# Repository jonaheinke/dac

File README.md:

# DAC with Headphone Amplifier

## Introduction

## Schematic preview

### Main schematic

### Left amplifier (right channel is identical)

### Power supply

### Front plate

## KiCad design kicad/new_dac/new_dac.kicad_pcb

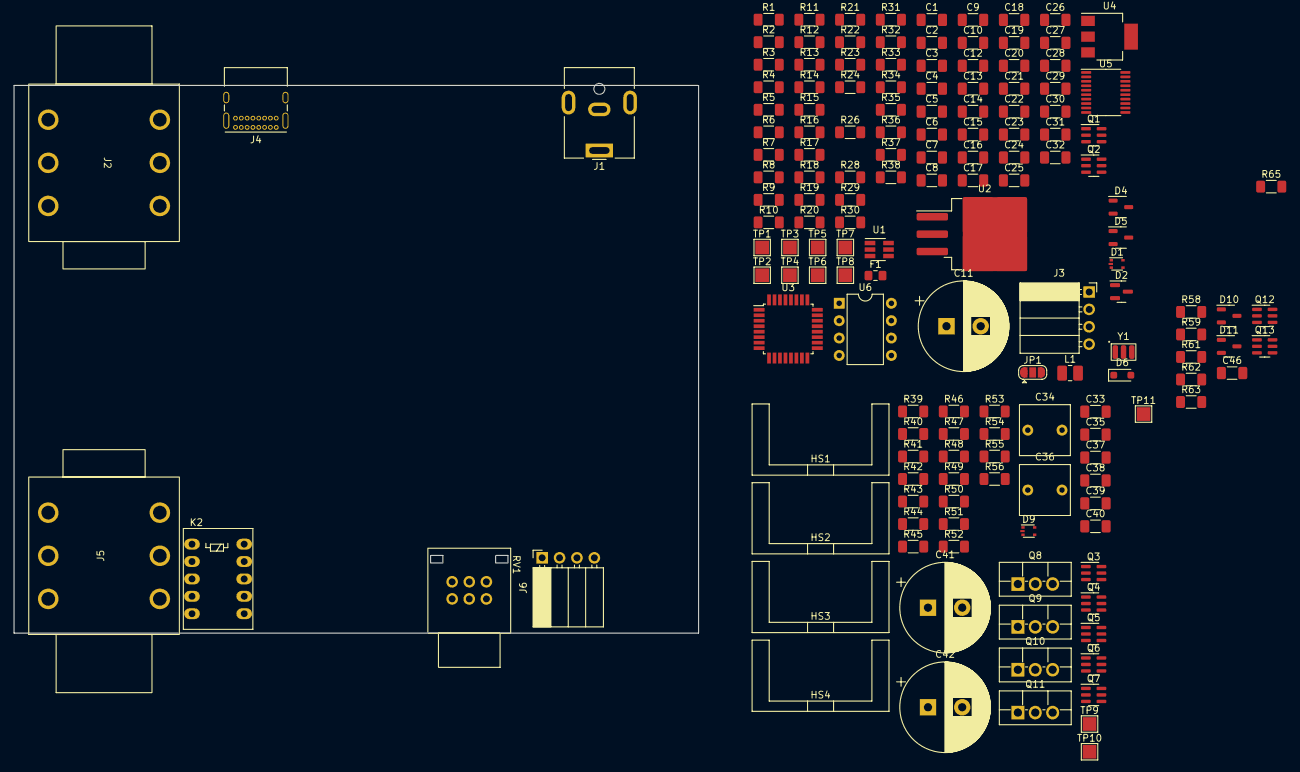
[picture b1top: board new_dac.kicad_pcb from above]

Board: 4 copper layers, 100.0 x 80.0 mm, 158 parts (1 on the bottom side), 92 nets, no tracks yet.

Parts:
C1, C7, C9, C10, C14, C15, C18, C21, C32, C37, C38: 100n; C_1206_3216Metric_Pad1.33x1.80mm_HandSolder
C2, C5, C6, C8, C12, C13, C16, C19, C22, C23, C24, C28, C29, C35: 10u; C_1206_3216Metric_Pad1.33x1.80mm_HandSolder
C3, C4, C25, C30, C31: 15n; C_1206_3216Metric_Pad1.33x1.80mm_HandSolder
C11: 470u; CP_Radial_D13.0mm_P5.00mm
C17, C20, C26, C46: 2u2; C_1206_3216Metric_Pad1.33x1.80mm_HandSolder
C27: 1n; C_1206_3216Metric_Pad1.33x1.80mm_HandSolder
C33: 4u7; C_1206_3216Metric_Pad1.33x1.80mm_HandSolder
C34: 4u7; C_Rect_L7.2mm_W7.2mm_P5.00mm_FKS2_FKP2_MKS2_MKP2
C36: 10u; C_Rect_L7.2mm_W7.2mm_P5.00mm_FKS2_FKP2_MKS2_MKP2
C39, C40: 470u; C_1206_3216Metric_Pad1.33x1.80mm_HandSolder
C41, C42: 10u; CP_Radial_D13.0mm_P5.00mm
D1, D9: QUAD_TVS_5V; SOT-665
D2, D7: DUAL_TVS_15V; SOT-23
D4, D5: D; SOT-23-3
D6: D; D_SOD-323_HandSoldering
D10, D11: SOT-23-3
F1: 500mA; Fuse_0805_2012Metric_Pad1.15x1.40mm_HandSolder
HS1, HS2, HS3, HS4: Heatsink; Heatsink_Boyd_507302B00000G
J1: USB_C_Receptacle_USB2.0; BarrelJack_CUI_PJ-063AH_Horizontal
J2: Barrel_Jack_Switch; Audio_Jack_SJ-6307
J3: Conn_01x04; PinSocket_1x04_P2.54mm_Horizontal
J4: USB_C_Receptacle_USB2.0; USB_C_Receptacle_GCT_USB4085
J5: AudioJack3_Switch; Audio_Jack_SJ-6307
J6: AudioJack3_Switch; PinSocket_1x04_P2.54mm_Horizontal
JP1: Ground_Jumper; SolderJumper-3_P1.3mm_Open_RoundedPad1.0x1.5mm
K2: DPDT_Relay; Relay_DPDT_FRT5
L1: 6u8; L_1008_2520Metric_Pad1.43x2.20mm_HandSolder
Q1, Q5, Q6, Q7, Q12: BCM56DS; SC-74-6_1.5x2.9mm_P0.95mm
Q2, Q3, Q4, Q13: BCM53DS; SC-74-6_1.5x2.9mm_P0.95mm
Q8, Q9, Q10, Q11: 2SC4511; TO-220F-3_Vertical
R1, R2: 5k1; R_1206_3216Metric_Pad1.30x1.75mm_HandSolder
R3, R7, R30, R39, R41: 1k5; R_1206_3216Metric_Pad1.30x1.75mm_HandSolder
R4, R5: 22; R_1206_3216Metric_Pad1.30x1.75mm_HandSolder
R6, R10: 430k; R_1206_3216Metric_Pad1.30x1.75mm_HandSolder
R8, R9, R32: 1M; R_1206_3216Metric_Pad1.30x1.75mm_HandSolder
R11: 3k9; R_1206_3216Metric_Pad1.30x1.75mm_HandSolder
R12, R24, R31: 680; R_1206_3216Metric_Pad1.30x1.75mm_HandSolder
R13, R16, R19, R22, R33, R34, R37, R38, R43, R45, R55, R56, R61: 22k; R_1206_3216Metric_Pad1.30x1.75mm_HandSolder
R14, R15, R20, R53, R54, R62: 100k; R_1206_3216Metric_Pad1.30x1.75mm_HandSolder
R17, R18, R26, R51, R52: 15; R_1206_3216Metric_Pad1.30x1.75mm_HandSolder
R21, R44, R46, R63: 10k; R_1206_3216Metric_Pad1.30x1.75mm_HandSolder
R23, R47, R48, R65: 2k2; R_1206_3216Metric_Pad1.30x1.75mm_HandSolder
R28, R29, R49, R50: 8R2; R_1206_3216Metric_Pad1.30x1.75mm_HandSolder
R35, R36, R40, R42: 4k3; R_1206_3216Metric_Pad1.30x1.75mm_HandSolder
R58, R59: 47k; R_1206_3216Metric_Pad1.30x1.75mm_HandSolder
RV1: 10k; RK09L12B
TP1: VBUS; TestPoint_Pad_2.0x2.0mm
TP2: +24; TestPoint_Pad_2.0x2.0mm
TP3: +5V; TestPoint_Pad_2.0x2.0mm
TP4: +22; TestPoint_Pad_2.0x2.0mm
TP5: GND; TestPoint_Pad_2.0x2.0mm
TP6, TP11: +3V3; TestPoint_Pad_2.0x2.0mm
TP7: -3V3; TestPoint_Pad_2.0x2.0mm
TP8: 1V8; TestPoint_Pad_2.0x2.0mm
TP9: VAS_L; TestPoint_Pad_2.0x2.0mm
TP10: VAS_R; TestPoint_Pad_2.0x2.0mm
U1: BD9G101G; SOT-23-6_Handsoldering
U2: LT3088; TO-263-3_TabPin2
U3: PCM2706CPJTR; TQFP-32_7x7mm_P0.8mm
U4: TLV1117LV-33; SOT-223-3_TabPin2
U5: PCM5102A; TSSOP-20_4.4x6.5mm_P0.65mm
U6: LM555xN; DIP-8_W7.62mm
Y1: 12MHz±0.05%; Resonator_Murata

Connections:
+3V3: C7.2, C12.1, C13.1, C14.1, C15.1, C16.1, C21.1, C22.1, R3.2, R7.2, TP6.1, TP11.1, U3.10 (TEST), U3.16 (PSEL), U3.21 (VDD), U3.24 (VBUS), U4.2 (VO), U5.1 (CPVDD), U5.8 (AVDD), U5.20 (DVDD)
+5V: C6.1, C10.1, L1.2, R11.1, R23.1, R33.1, TP3.1, U4.3 (VI), U6.4 (R), U6.8 (VCC)
+20Vreg: C5.1, C11.1, Q3.5 (E1), Q4.5 (E1), Q5.3 (C2), Q6.3 (C2), Q8.2 (C), Q10.2 (C), R13.1, R39.1, R41.1, R47.1, R48.1, TP4.1, U2.2 (OUT)
+24V: C2.1, C26.1, C46.1, J3.1, Q2.5 (E1), Q13.4 (E2), R6.1, R16.1, R20.1, R61.1, R62.1, TP2.1, U1.4 (EN), U1.5 (VCC), U2.3 (IN)
/AMP_L: C39.2, R14.1, R17.1
/AMP_R: C40.2, R15.1, R18.1
/AUDIO_OUT_L: D7.2 (A2), J5.T, K2.8, R28.2
/AUDIO_OUT_R: D7.1 (A1), J5.R, K2.3, R29.2
/BCK: U3.19 (FUNC1), U5.13 (BCK)
/BST: C4.1, U1.1 (BST)
/CAPM: C17.2, U5.4 (CAPM)
/CAPP: C17.1, U5.2 (CAPP)
/CONN_D+: D1.4 (A3), J4.A6 (D+), J4.B6 (D+), R3.1, R5.1
/CONN_D-: D1.3 (A2), J4.A7 (D-), J4.B7 (D-), R4.1
/D+: R5.2, U3.23 (D+)
/D-: R4.2, U3.22 (D-)
/DAC_OUT_L: D9.1 (A1), U5.6 (OUTL)
/DAC_OUT_R: D9.4 (A3), U5.7 (OUTR)
/DATA: U3.17 (DOUT), U5.14 (DIN)
/DC_FUSED: D2.2 (A2), F1.2
/DC_LP_L: C23.1, D4.2 (A), R14.2
/DC_LP_R: C24.1, D5.2 (A), R15.2
/DT: R7.1, U3.15 (DT)
/FEEDBACK: C10.2, R11.2, R12.1, U1.3 (FB)
/LDOO: C18.1, C19.1, TP8.1, U5.18 (LDOO)
/LRCK: U3.5 (FUNC0), U5.15 (LRCK)
/PROT_ARC_L: C28.2, R28.1
/PROT_ARC_R: C29.2, R29.1
/RELAY: K2.1, Q2.6 (C1), R65.1
/RLY_IN_L: C28.1, K2.7, R17.2, R19.2
/RLY_IN_R: C29.1, K2.4, R18.2, R22.2
/Reg_Set: C3.1, R10.1, U2.1 (SET)
/SCK: U3.18 (FUNC2), U5.12 (SCK)
/SSPND: J3.2, U3.11 (~SSPND), U5.17 (XSMT)
/SWITCHING: C4.2, L1.1, U1.6 (LX)
/USB_SHIELD: D1.2 (C), J4.S1 (SHIELD), JP1.3 (B)
/VCCP: C9.2, U3.2 (VCCP)
/VCOM: C8.2, U3.32 (VCOM)
/VNEG: C20.1, TP7.1, U5.5 (VNEG)
/XTI: R8.1, U3.12 (XTI), Y1.1
/XTO: R8.2, U3.13 (XTO), Y1.3
/amplifier/AUDIO_IN_L: D9.3 (A2), RV1.1
/amplifier/AUDIO_IN_R: D9.5 (A4), RV1.4
/amplifier/FB_L: Q5.1 (B1), R35.2, R43.2, R44.1
/amplifier/FB_R: Q6.1 (B1), R36.2, R45.2, R46.1
/amplifier/OPS_L: C39.1, Q8.3 (E), Q9.2 (C), R43.1, R51.1
/amplifier/OPS_R: C40.1, Q10.3 (E), Q11.2 (C), R45.1, R52.1
/amplifier/VAS_L: Q3.3 (C2), Q5.2 (B2), Q5.6 (C1), TP9.1
/amplifier/VAS_R: Q4.3 (C2), Q6.2 (B2), Q6.6 (C1), TP10.1
/old_design/DC_LP_L: C41.1, R53.2, R55.1
/old_design/DC_LP_R: C42.1, R54.2, R56.1
/old_design/DC_NEG: D10.1 (A), D11.1 (A), Q13.1 (B1)
/old_design/DC_POS: D10.3 (K), D11.3 (K), Q12.1 (B1)
/old_design/DC_VD_L: D10.2 (common), R55.2, R58.1
/old_design/DC_VD_R: D11.2 (common), R56.2, R59.1
GND: C2.2, C3.2, C5.2, C6.2, C11.2, C12.2, C35.2, C36.2, C37.2, C38.2, D2.1 (A1), D7.3 (common), D9.2 (C), J3.4, J5.S, J5.SN, JP1.1 (A), Q7.4 (E2), Q7.5 (E1), R6.2, R10.2, R12.2, R13.2, R19.1, R22.1, R37.2, R38.2, R40.2, R42.2, R44.2, R46.2, R49.2, R50.2, RV1.3, RV1.6, TP5.1, U1.2 (GND), U4.1 (GND)
GNDD: C1.2, C7.1, C8.1, C9.1, C13.2, C14.2, C15.2, C16.2, C18.2, C19.2, C20.2, C21.2, C22.2, C23.2, C24.2, C25.2, C27.2, C30.2, C32.2, C41.2, C42.2, D1.5 (A4), D6.2 (A), J4.A1 (GND), J4.A12 (GND), J4.B1 (GND), J4.B12 (GND), JP1.2 (C), K2.2, K2.9, K2.10, Q1.4 (E2), Q1.5 (E1), Q12.4 (E2), Q12.5 (E1), Q13.6 (C1), R1.2, R2.2, R9.1, R31.2, R32.2, R34.2, R58.2, R59.2, U3.1 (PGND), U3.9 (FSEL), U3.20 (DGND), U3.25 (ZGND), U3.26 (AGNDL), U3.31 (AGNDR), U5.3 (CPGND), U5.9 (AGND), U5.10 (DEMP), U5.11 (FLT), U5.16 (FMT), U5.19 (DGND), U6.1 (GND), Y1.2
unnamed: C33.1, RV1.2
unnamed: C33.2, R35.1
unnamed: C34.1, RV1.5
unnamed: C34.2, R36.1
unnamed: C37.1, R51.2
unnamed: C38.1, R52.2
unnamed: D4.1 (K), D5.1 (K), Q1.1 (B1)
unnamed: D6.1 (K), R65.2
unnamed: C32.1, R32.1
unnamed: Q1.2 (B2), Q1.6 (C1), R16.2
unnamed: C26.2, Q1.3 (C2), R21.2
unnamed: Q2.1 (B1), R20.2, R21.1
unnamed: Q3.1 (B1), Q3.4 (E2), R39.2
unnamed: Q3.2 (B2), Q3.6 (C1), R37.1
unnamed: Q4.1 (B1), Q4.4 (E2), R41.2
unnamed: Q4.2 (B2), Q4.6 (C1), R38.1
unnamed: C35.1, Q5.5 (E1), R40.1
unnamed: Q5.4 (E2), Q8.1 (B)
unnamed: C36.1, Q6.5 (E1), R42.1
unnamed: Q7.1 (B1), Q9.3 (E), R49.1
unnamed: Q7.6 (C1), Q9.1 (B), R47.2
unnamed: Q6.4 (E2), Q10.1 (B)
unnamed: Q7.3 (C2), Q11.1 (B), R48.2
unnamed: Q7.2 (B2), Q11.3 (E), R50.1
unnamed: Q12.2 (B2), Q12.6 (C1), Q13.5 (E1), R61.2
unnamed: C46.2, Q12.3 (C2), R63.2
unnamed: Q13.2 (B2), R62.2, R63.1
unnamed: C25.1, U6.5 (CV)
unnamed: R23.2, R24.1, U6.7 (DIS)
unnamed: R26.1, U6.3 (Q)
unnamed: C27.1, R24.2, U6.2 (TR), U6.6 (THR)
unnamed: C30.1, R26.2
unnamed: C31.2, R31.1
unnamed: R33.2, R34.1
VBUS: C1.1, D1.1 (A1), J4.A4 (VBUS), J4.A9 (VBUS), J4.B4 (VBUS), J4.B9 (VBUS), R9.2, TP1.1, U3.3 (HOST)

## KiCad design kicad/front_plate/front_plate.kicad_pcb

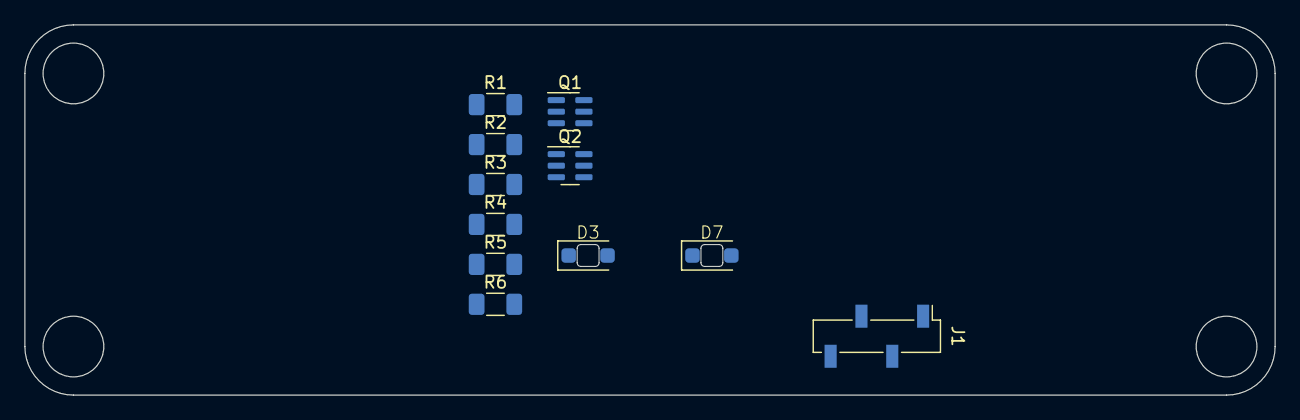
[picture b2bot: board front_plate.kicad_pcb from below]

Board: 2 copper layers, 103.0 x 30.5 mm, 11 parts (11 on the bottom side), 11 nets, no tracks yet.

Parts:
D3, D7: AMBER; LED_Harvatek_B2601
J1: Conn_01x04; PinSocket_1x04_P2.54mm_Vertical_SMD_Pin1Left
Q1, Q2: BCM56DS; SC-74-6_1.5x2.9mm_P0.95mm
R1: 47k; R_1206_3216Metric_Pad1.30x1.75mm_HandSolder
R2, R4, R5: 2k2; R_1206_3216Metric_Pad1.30x1.75mm_HandSolder
R3: 10k; R_1206_3216Metric_Pad1.30x1.75mm_HandSolder
R6: 4k3; R_1206_3216Metric_Pad1.30x1.75mm_HandSolder

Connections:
+24V: J1.1, R1.2, R3.2, R4.2, R5.2
/ANALOG: J1.3, Q1.1 (B1), R1.1, R2.2
/USB: J1.2, R6.1
GND: J1.4, Q1.4 (E2), Q1.5 (E1), Q2.4 (E2), R2.1
unnamed: D3.2 (A), R4.1
unnamed: D3.1 (K), Q1.3 (C2)
unnamed: D7.2 (A), R5.1
unnamed: D7.1 (K), Q2.6 (C1)
unnamed: Q1.2 (B2), Q1.6 (C1), Q2.2 (B2), R3.1
unnamed: Q2.1 (B1), R6.2
unnamed: Q2.3 (C2), Q2.5 (E1)

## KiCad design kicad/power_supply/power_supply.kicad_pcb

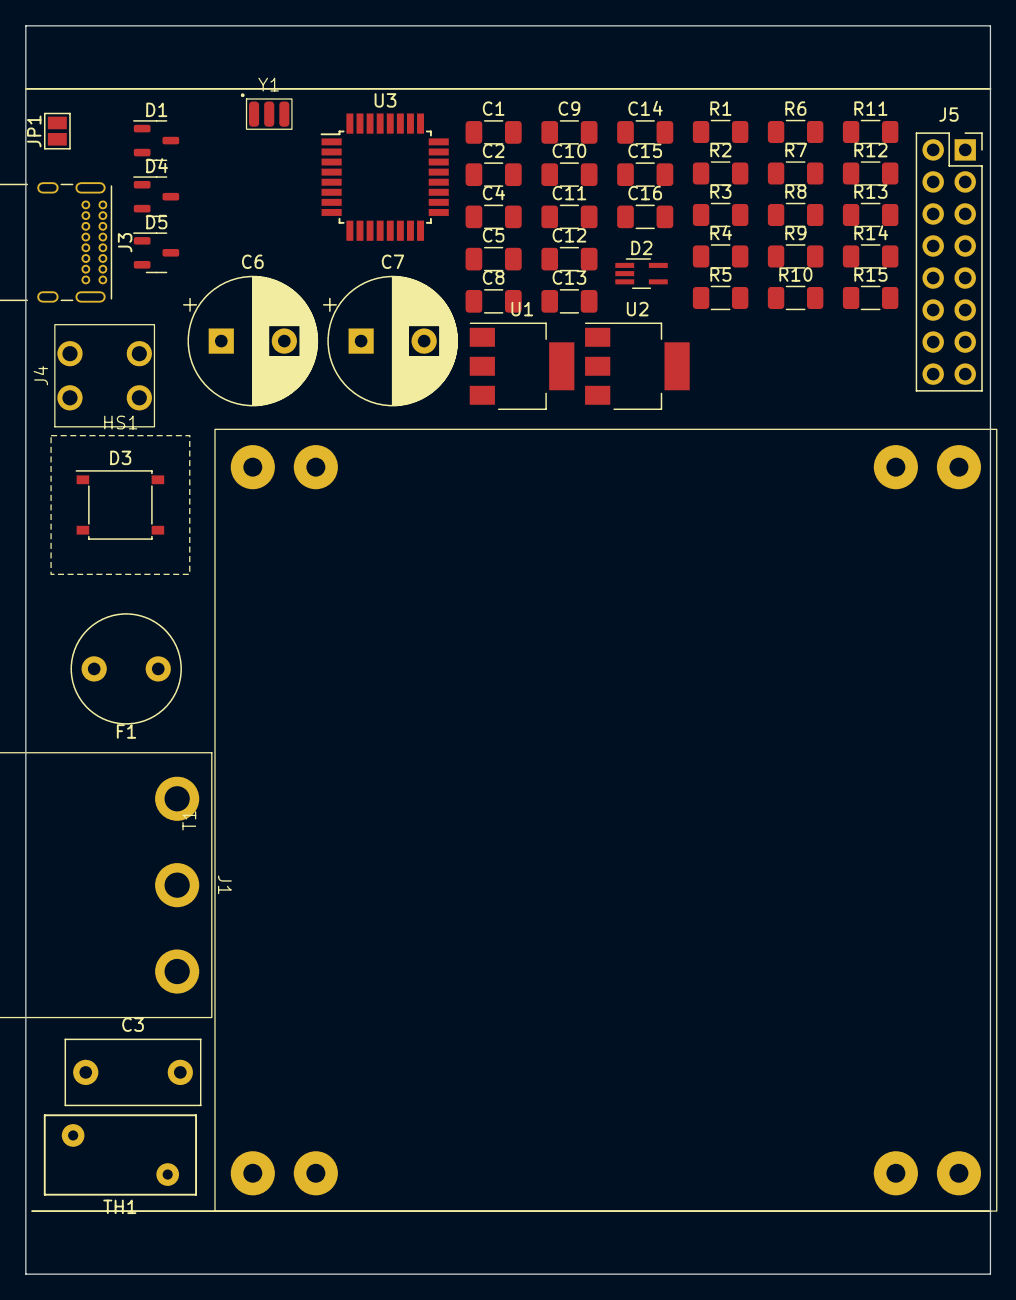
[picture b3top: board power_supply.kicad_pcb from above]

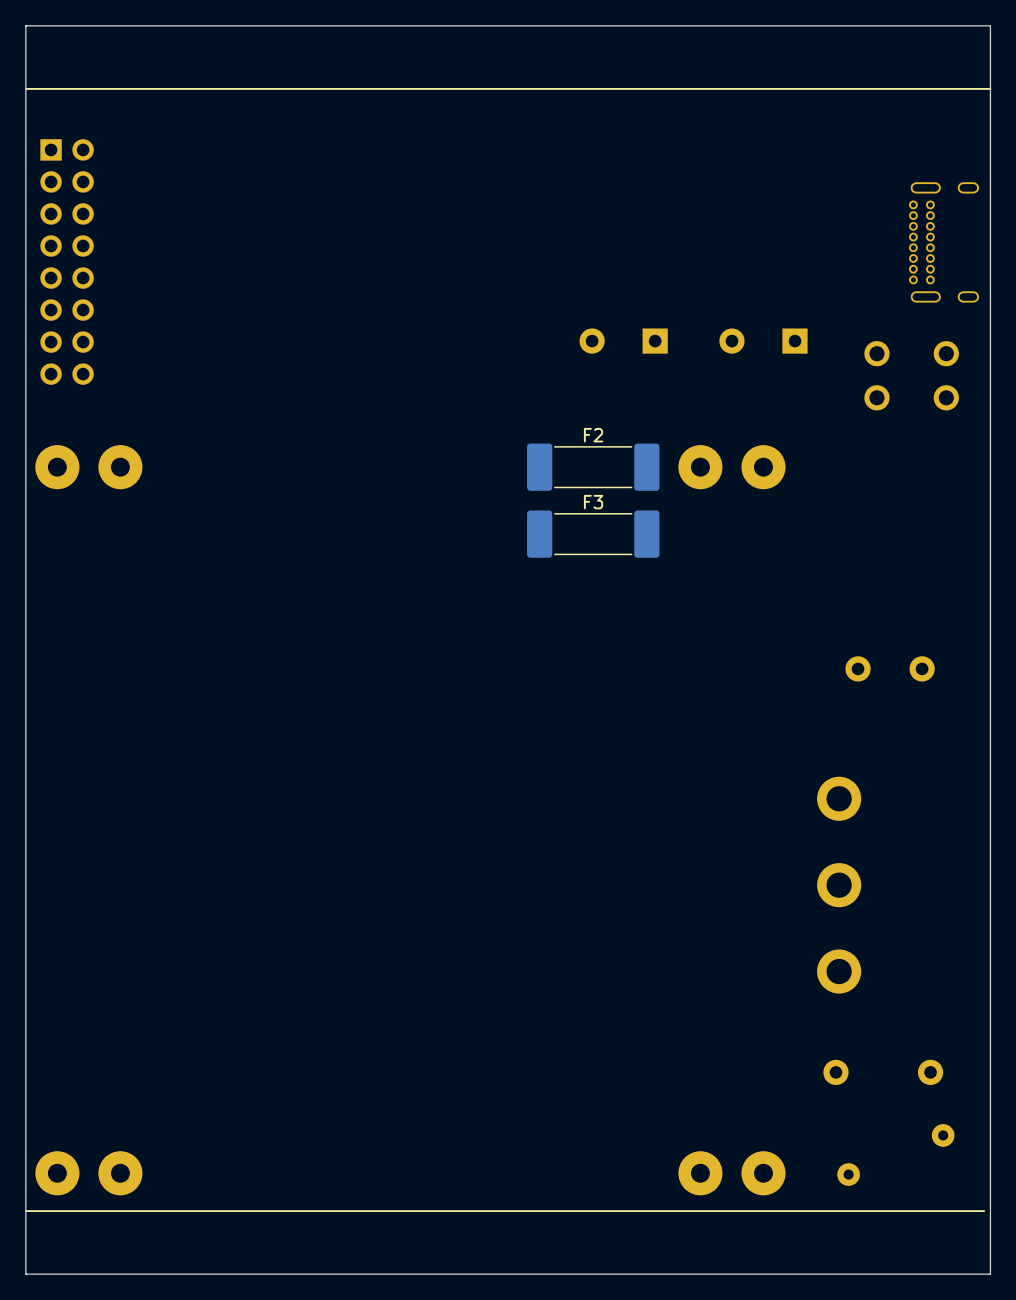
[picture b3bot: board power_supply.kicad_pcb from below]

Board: 2 copper layers, 76.5 x 99.0 mm, 51 parts (2 on the bottom side), 34 nets, no tracks yet.

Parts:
C1, C4, C8, C10, C13, C14: 100n; C_1206_3216Metric_Pad1.33x1.80mm_HandSolder
C2: 4n7; C_1206_3216Metric_Pad1.33x1.80mm_HandSolder
C3: 3n9; C_Disc_D10.5mm_W5.0mm_P7.50mm
C5: 3u3; C_1206_3216Metric_Pad1.33x1.80mm_HandSolder
C6, C7: 470u; CP_Radial_D10.0mm_P5.00mm
C9, C11, C12, C15, C16: 10u; C_1206_3216Metric_Pad1.33x1.80mm_HandSolder
D1, D4, D5: SOT-23-3
D2: D_TVS_Quadruple; SOT-353_SC-70-5_Handsoldering
D3: Diode_Bridge_Vishay_MBLS
F1: 80mA; Fuse_Littelfuse_372_D8.50mm
F2, F3: 500mA; Fuse_Schurter_UMT250
HS1: Heatsink; Heatsink_10x10
J1: Conn_WallSocket_Earth; WallSocket_Schurter_6160.0003
J3: USB_C_Receptacle_USB2.0; USB_C_Receptacle_GCT_USB4085
J4: Conn_01x02; WAGO_2086-11X2
J5: Conn_02x08_Odd_Even; PinSocket_2x08_P2.54mm_Vertical
JP1: Jumper_2_Open; SolderJumper-2_P1.3mm_Open_Pad1.0x1.5mm
R1, R6, R7: 22; R_1206_3216Metric_Pad1.30x1.75mm_HandSolder
R2: 33k; R_1206_3216Metric_Pad1.30x1.75mm_HandSolder
R3, R4: 5k1; R_1206_3216Metric_Pad1.30x1.75mm_HandSolder
R5, R8: 1k5; R_1206_3216Metric_Pad1.30x1.75mm_HandSolder
R9, R10: 10k; R_1206_3216Metric_Pad1.30x1.75mm_HandSolder
R11: 1M; R_1206_3216Metric_Pad1.30x1.75mm_HandSolder
R12, R15: 100; R_1206_3216Metric_Pad1.30x1.75mm_HandSolder
R13, R14: 1k1; R_1206_3216Metric_Pad1.30x1.75mm_HandSolder
T1: 70063K; Talema_Transformer_2P2S_25VA
TH1: MOV; RV_Disc_D12mm_W6.3mm_P7.5mm
U1: LM317_SOT-223; SOT-223-3_TabPin2
U2: LM337_SOT223; SOT-223-3_TabPin2
U3: PCM2706CPJTR; TQFP-32_7x7mm_P0.8mm
Y1: 12MHz±0.05%; Resonator_Murata

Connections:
+3V3: C8.2, R5.2, R8.2, U3.10 (TEST), U3.16 (PSEL), U3.21 (VDD)
+20Vreg: C13.1, C15.1, D4.2 (common), J5.1, R12.1, U1.2 (VO)
+25V: C6.1, D4.3 (K), F2.2, J5.2, R9.1, U1.3 (VI)
-20Vreg: C14.2, C16.2, D5.2 (common), J5.5, R15.2, U2.3 (VO)
-25V: C7.2, D5.1 (A), F3.2, J5.6, R10.2, U2.2 (VI)
/BCK: J5.15, U3.19 (FUNC1)
/CONN_D+: D2.4 (A3), J3.A6 (D+), J3.B6 (D+), R5.1, R7.1
/CONN_D-: D2.3 (A2), J3.A7 (D-), J3.B7 (D-), R6.1
/D+: R7.2, U3.23 (D+)
/D-: R6.2, U3.22 (D-)
/DATA: J5.10, U3.17 (DOUT)
/DT: R8.1, U3.15 (DT)
/LIVE: J4.2, T1.1
/LRCK: J5.16, U3.5 (FUNC0)
/NEUTRAL: C3.2, J1.2 (AC_N), TH1.2
/SCK: J5.14, U3.18 (FUNC2)
/SSPND: J5.11, U3.11 (~SSPND)
/VCOM: C9.2, U3.32 (VCOM)
/V_{rect}+: D3.1 (+), F2.1
/V_{rect}-: D3.3 (-), F3.1
/XTI: R11.1, U3.12 (XTI), Y1.1
/XTO: R11.2, U3.13 (XTO), Y1.3
GND: C1.1, C6.2, C7.1, C11.2, C12.1, C13.2, C14.1, C15.2, C16.1, D1.2 (A), J5.3, J5.4, J5.12, J5.13, R1.2, R9.2, R10.1, R13.2, R14.1
GNDD: C2.2, C4.1, C5.1, C8.1, C9.1, C10.1, D2.5 (A4), J3.A1 (GND), J3.A12 (GND), J3.B1 (GND), J3.B12 (GND), JP1.1 (A), R2.1, R3.2, R4.2, U3.1 (PGND), U3.3 (HOST), U3.9 (FSEL), U3.20 (DGND), U3.25 (ZGND), Y1.2
unnamed: C2.1, D2.2 (C), J3.S1 (SHIELD), JP1.2 (B), R2.2
unnamed: C11.1, D4.1 (A), R12.2, R13.1, U1.1 (ADJ)
unnamed: C12.2, D5.3 (K), R14.2, R15.1, U2.1 (ADJ)
unnamed: F1.1, J1.1 (AC_P)
unnamed: C1.2, D1.1 (K), D1.3 (K), J1.3 (EARTH), R1.1
unnamed: J3.A5 (CC1), R3.1
unnamed: J3.B5 (CC2), R4.1
unnamed: C3.1, F1.2, J4.1, TH1.1
unnamed: C10.2, U3.2 (VCCP)
VBUS: C4.2, C5.2, D2.1 (A1), J3.A4 (VBUS), J3.A9 (VBUS), J3.B4 (VBUS), J3.B9 (VBUS), J5.9, U3.24 (VBUS)

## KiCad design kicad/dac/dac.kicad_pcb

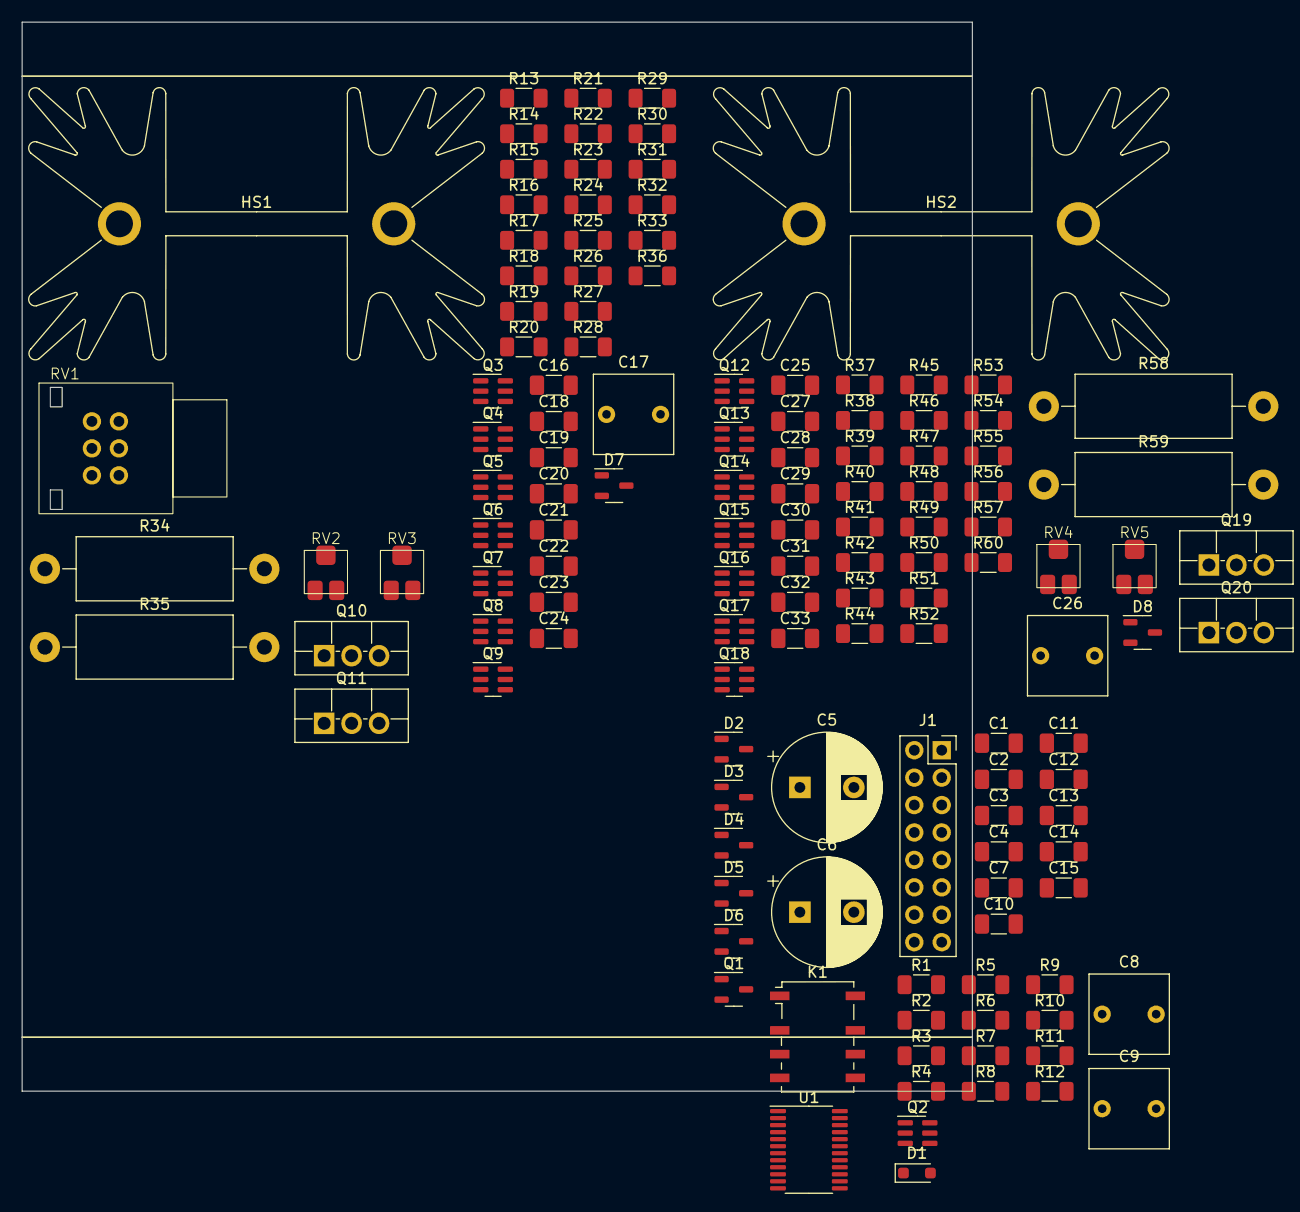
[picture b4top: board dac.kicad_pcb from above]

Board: 4 copper layers, 88.0 x 99.0 mm, 131 parts (0 on the bottom side), 89 nets, no tracks yet.

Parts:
C1, C2, C4, C11, C12, C13, C14, C15, C18, C19, C21, C22, C23, C27, C28, C30, C31, C32: 10u; C_1206_3216Metric_Pad1.33x1.80mm_HandSolder
C3, C10: 100n; C_1206_3216Metric_Pad1.33x1.80mm_HandSolder
C5, C6: 470u; CP_Radial_D10.0mm_P5.00mm
C7: 3u3; C_1206_3216Metric_Pad1.33x1.80mm_HandSolder
C8, C9, C17, C26: 3u3; C_Rect_L7.2mm_W7.2mm_P5.00mm_FKS2_FKP2_MKS2_MKP2
C16, C24, C25, C33: 20n; C_1206_3216Metric_Pad1.33x1.80mm_HandSolder
C20, C29: 30p; C_1206_3216Metric_Pad1.33x1.80mm_HandSolder
D1: D; D_SOD-323_HandSoldering
D2, D3, D4, D5, D6, D7, D8: SOT-23-3
HS1, HS2: Heatsink; Heatsink_Fischer_SK129-STS_42x25mm_2xDrill2.5mm
J1: Conn_02x08_Odd_Even; PinSocket_2x08_P2.54mm_Vertical
K1: Relay; Relay_DPDT_Omron_G6K-2F-Y
Q1: MMBT5551; SOT-23-3
Q2, Q3, Q4, Q7, Q9, Q12, Q13, Q16, Q18: BCM53DS; SC-74-6_1.5x2.9mm_P0.95mm
Q5, Q6, Q8, Q14, Q15, Q17: BCM56DS; SC-74-6_1.5x2.9mm_P0.95mm
Q10, Q19: 2SC4511; TO-220F-3_Vertical
Q11, Q20: 2SA1725; TO-220F-3_Vertical
R1: 47k; R_1206_3216Metric_Pad1.30x1.75mm_HandSolder
R2, R3, R11, R12: 10k; R_1206_3216Metric_Pad1.30x1.75mm_HandSolder
R4, R5, R10: 100k; R_1206_3216Metric_Pad1.30x1.75mm_HandSolder
R6, R7, R36, R60: 16; R_1206_3216Metric_Pad1.30x1.75mm_HandSolder
R8, R9: 2; R_1206_3216Metric_Pad1.30x1.75mm_HandSolder
R13, R18, R20, R29, R37, R42, R44, R53: 68; R_1206_3216Metric_Pad1.30x1.75mm_HandSolder
R14, R15, R24, R26, R38, R39, R48, R50: 27k; R_1206_3216Metric_Pad1.30x1.75mm_HandSolder
R16, R17, R21, R22, R28, R40, R41, R45, R46, R52: 430; R_1206_3216Metric_Pad1.30x1.75mm_HandSolder
R19, R43: 680; R_1206_3216Metric_Pad1.30x1.75mm_HandSolder
R23, R25, R27, R47, R49, R51: 2k2; R_1206_3216Metric_Pad1.30x1.75mm_HandSolder
R30, R54: 12; R_1206_3216Metric_Pad1.30x1.75mm_HandSolder
R31, R55: 22; R_1206_3216Metric_Pad1.30x1.75mm_HandSolder
R32, R33, R56, R57: 33; R_1206_3216Metric_Pad1.30x1.75mm_HandSolder
R34, R35, R58, R59: 2; R_Axial_DIN0614_L14.3mm_D5.7mm_P20.32mm_Horizontal
RV1: 10k; RK09L12B
RV2, RV4: 100; TC33
RV3, RV5: 500; TC33
U1: CS4349; TSSOP-24_4.4x7.8mm_P0.65mm

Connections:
+20Vreg: C19.1, C22.1, C28.1, C31.1, J1.1, Q4.5 (E), Q7.5 (E), Q13.5 (E), Q16.5 (E), R19.2, R29.2, R43.2, R53.2
+25V: C5.1, C8.2, D5.3 (K), D6.3 (K), J1.2, Q8.3 (C), Q10.2 (C), Q17.3 (C), Q19.2 (C)
-20Vreg: C18.1, C21.1, C27.1, C30.1, J1.5, R16.1, R22.1, R25.1, R31.1, R40.1, R46.1, R49.1, R55.1
-25V: C6.2, C9.1, D5.1 (A), D6.1 (A), J1.6, Q9.2 (B), Q9.3 (C), Q9.4 (E), Q9.6 (C), Q11.2 (C), Q18.2 (B), Q18.3 (C), Q18.4 (E), Q18.6 (C), Q20.2 (C)
/AMP_L: C12.1, D7.2 (common), K1.8, R2.2, R24.2, R32.1, R33.2, R34.2, R35.1, R36.2
/AMP_R: C13.1, D8.2 (common), K1.5, R3.2, R48.2, R56.1, R57.2, R58.2, R59.1, R60.2
/DAC_L: R13.1, U1.15 (AOUTA)
/DAC_R: R37.1, U1.22 (AOUTB)
/DATA: J1.10, U1.11 (SDIN)
/DC_LP_L: C14.1, D2.2 (common), R4.2
/DC_LP_R: C15.1, D3.2 (common), R5.2
/LRCK: J1.16, U1.12 (LRCK)
/OUT_L: D6.2 (common), R4.1, R8.2
/OUT_R: D5.2 (common), K1.4, R5.1, R9.2
/POPGUARD: R1.2, U1.8 (POPGUARD/TSTO)
/PROT_ARC_L: C12.2, R8.1
/PROT_ARC_R: C13.2, R9.1
/RLY+: D1.1 (K), K1.1
/RLY_NC_R: K1.3, R7.2
/SCK: J1.14, U1.10 (SCLK)
/VBIAS: C4.2, U1.17 (VBIAS)
/VD_FILT: C10.1, C11.1, U1.6 (VD_FILT)
/VQ: C7.1, U1.20 (VQ)
/amplifier_left/CC_IPS_L: Q4.3 (C), R18.2, R20.2, RV2.2
/amplifier_left/CC_VAS_L: Q7.3 (C), R27.2, R30.1
/amplifier_left/CM_L: Q3.3 (C), Q5.1 (B), Q5.2 (B), Q5.3 (C)
/amplifier_left/FB_L: Q3.2 (B), R23.2, R24.1
/amplifier_left/INPUT_L: Q3.1 (B), R14.2, RV1.2
/amplifier_left/IPS_L: C20.1, Q3.6 (C), Q5.6 (C), Q6.1 (B)
/amplifier_left/VAS_DARL_L: Q6.2 (B), Q6.5 (E), R25.2
/amplifier_left/V_{OPS}+_L: Q8.4 (E), Q10.1 (B), R32.2
/amplifier_left/V_{OPS}-_L: Q9.5 (E), Q11.1 (B), R33.1
/amplifier_left/V_{bias}+_L: C23.1, D7.3 (K), Q8.2 (B), Q8.6 (C), R30.2
/amplifier_left/V_{bias}-_L: C20.2, C23.2, D7.1 (A), Q6.3 (C), Q8.5 (E), Q9.1 (B), RV3.2, RV3.3
/amplifier_left/V_{bias}B_L: Q8.1 (B), R27.1, R28.2
/amplifier_left/V_{q}+_L: Q10.3 (E), R34.1
/amplifier_left/V_{q}-_L: Q11.3 (E), R35.2
/amplifier_left/ZOBEL_L: C24.2, R36.1
/amplifier_right/CC_IPS_R: Q13.3 (C), R42.2, R44.2, RV4.2
/amplifier_right/CC_VAS_R: Q16.3 (C), R51.2, R54.1
/amplifier_right/CM_R: Q12.3 (C), Q14.1 (B), Q14.2 (B), Q14.3 (C)
/amplifier_right/FB_L: Q12.2 (B), R47.2, R48.1
/amplifier_right/INPUT_R: Q12.1 (B), R38.2, RV1.5
/amplifier_right/IPS_R: C29.1, Q12.6 (C), Q14.6 (C), Q15.1 (B)
/amplifier_right/VAS_DARL_R: Q15.2 (B), Q15.5 (E), R49.2
/amplifier_right/V_{OPS}+_R: Q17.4 (E), Q19.1 (B), R56.2
/amplifier_right/V_{OPS}-_R: Q18.5 (E), Q20.1 (B), R57.1
/amplifier_right/V_{bias}+_R: C32.1, D8.3 (K), Q17.2 (B), Q17.6 (C), R54.2
/amplifier_right/V_{bias}-_R: C29.2, C32.2, D8.1 (A), Q15.3 (C), Q17.5 (E), Q18.1 (B), RV5.2, RV5.3
/amplifier_right/V_{bias}B_R: Q17.1 (B), R51.1, R52.2
/amplifier_right/V_{q}+_R: Q19.3 (E), R58.1
/amplifier_right/V_{q}-_R: Q20.3 (E), R59.2
/amplifier_right/ZOBEL_R: C33.2, R60.1
GND: C1.2, C2.2, C3.2, C5.2, C6.1, C7.2, C8.1, C9.2, C10.2, C11.2, C14.2, C15.2, C16.1, C18.2, C19.2, C21.2, C22.2, C24.1, C25.1, C27.2, C28.2, C30.2, C31.2, C33.1, D4.2 (common), J1.3, J1.4, J1.12, J1.13, Q6.6 (C), Q15.6 (C), R2.1, R3.1, R6.1, R7.1, R14.1, R15.1, R23.1, R26.1, R38.1, R39.1, R47.1, R50.1, RV1.3, RV1.6, U1.1 (DIF2/AD1/CDOUT), U1.2 (DEM/AD0/~CS), U1.4 (DIF1/SCL/CCLK), U1.7 (GND), U1.19 (GND)
unnamed: C16.2, C17.1, R13.2
unnamed: C17.2, RV1.1
unnamed: C25.2, C26.1, R37.2
unnamed: C26.2, RV1.4
unnamed: D2.1 (A), D3.1 (A), D4.1 (A), Q2.2 (B)
unnamed: D2.3 (K), D3.3 (K), D4.3 (K), Q1.1 (B)
unnamed: Q1.3 (C), R11.2
unnamed: Q1.2 (E), Q2.3 (C)
unnamed: Q2.1 (B), R10.2, R11.1
unnamed: Q2.4 (E), R12.1
unnamed: Q3.5 (E), R17.1
unnamed: Q3.4 (E), R21.2
unnamed: Q4.1 (B), Q4.4 (E), R19.1
unnamed: Q4.2 (B), Q4.6 (C), R15.2
unnamed: Q5.5 (E), R16.2
unnamed: Q5.4 (E), R22.2
unnamed: Q6.4 (E), R31.2
unnamed: Q7.1 (B), Q7.4 (E), R29.1
unnamed: Q7.2 (B), Q7.6 (C), R26.2
unnamed: Q12.5 (E), R41.1
unnamed: Q12.4 (E), R45.2
unnamed: Q13.1 (B), Q13.4 (E), R43.1
unnamed: Q13.2 (B), Q13.6 (C), R39.2
unnamed: Q14.5 (E), R40.2
unnamed: Q14.4 (E), R46.2
unnamed: Q15.4 (E), R55.2
unnamed: Q16.1 (B), Q16.4 (E), R53.1
unnamed: Q16.2 (B), Q16.6 (C), R50.2
unnamed: R17.2, R18.1, RV2.1
unnamed: R20.1, R21.1, RV2.3
unnamed: R28.1, RV3.1
unnamed: R41.2, R42.1, RV4.1
unnamed: R44.1, R45.1, RV4.3
unnamed: R52.1, RV5.1
VBUS: C1.1, C2.1, C3.1, C4.1, J1.9, R1.1, U1.3 (DIF0/SDA/CDIN), U1.5 (VLC), U1.9 (VLS), U1.18 (VA)

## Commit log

2023-03-18 added PCB manufacturer evaluation added temporary first schematic design
2023-03-19 added mono amplifier and tvs diodes
2023-03-26 split power supply to different board
2023-05-12 completed power supply footprints and placement

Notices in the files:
kicad/dac/dac.kicad_pcb:
License: MIT License
kicad/new_dac/new_dac.kicad_pcb:
License: MIT
